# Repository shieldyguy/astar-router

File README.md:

# astar: a fast grid A* board router

A library and one binary over it, Rust, no dependencies. A scene goes in, a plan comes out.

    ./install.sh                  (cargo build --release, then ~/.local/bin/astar; CLAUDE.md has the rest)
    target/release/astar route IN.kicad_pcb -o OUT.kicad_pcb     a board in, the routed board out
    target/release/astar route SCENE.json PLAN.json [-v] [--strict]
    target/release/astar scene IN.kicad_pcb [-o SCENE.json]      the board as a scene
    target/release/astar lay BOARD.kicad_pcb PLAN.json -o OUT.kicad_pcb      a plan laid on its board
    target/release/astar --passes          the passes of a run, in order; --skip NAME leaves one out

It exits 0 when every net is joined, 1 when nets are open, 2 when the input could not be taken (and says
why), 3 when a width was narrowed and `--strict` was given. Every run checks the plan it wrote with
`astar check` before it reports: copper that breaks a rule, or a net called joined that is not, is
printed and the run exits 4 (a fault in astar, never in the board). It exits 5 when every net is joined
but KiCad will find fault that astar could not help: a custom rule it did not read that may ask more than
it kept, or a short the board came with (a pad lying on another net's copper); the lines say which. `astar SCENE.json PLAN.json` is the
old way to say the same and exits 0 whenever it wrote a plan the check finds no fault with. `docs/scene.md` is the scene, `docs/hooks.md` is how a
track adds a pass, a job kind, a cost term, a copper kind or a report entry.

astar reads a KiCad board itself (`src/io/`: KiCad 7 to the house 10.99, nets by number or by name) and
writes the plan back onto it: new copper in the file's own dialect, everything else byte for byte, the
`.kicad_pro`, `.kicad_dru` and `.kicad_prl` copied beside it unchanged. `docs/parity.md` says where its scene
differs from the house KiCad's export and why (`python3 parity/parity.py`); `python3 parity/formats.py` reads,
routes, writes and reopens a board of each file format.

`SCENE.json` and `PLAN.json` are router-bench's contract (its `CONTRACT.md`): pads, holes, outline, rules and
nets in; tracks, vias and poured planes per net out. `bench/astar.py` is the bench adapter (copy it to
`router-bench/routers/`).

## Where it stands

router-bench's five boards, judged by KiCad's DRC (`./gate.sh`, 2026-11-22). astar ran on a 2-core cloud
machine; the other two columns are the bench scoreboard's, recorded on the Mac. This repo carries dock and
g474 of the five; the other three are routed where a router-bench checkout is beside it. What astar does not
do yet is in CLAUDE.md; `corpus/SCOREBOARD.md` is the wider corpus at the same commit: 58 of 80 boards whole
with no new DRC error (the house's and the fork's own: 38 of 41; the rest are KRT's fixtures, KiCad's demos
and open boards, most of them BGA boards astar does not fan out).

| board | nets | astar | landed | new DRC | track mm | vias | krt_better | topo |
|-------|-----:|------:|-------:|--------:|---------:|-----:|-----------:|-----:|
| dock  |   28 | 2.0 s |  28/28 | 0 |  446 |  55 |  69.5 s, 443 mm |  0.1 s, 509 mm |
| g474  |   41 | 0.1 s |  41/41 | 0 |  739 | 113 |  19.4 s, 738 mm |  0.5 s, 927 mm |
| ccb   |   47 | 0.5 s |  47/47 | 0 | 1097 | 119 |  33.5 s, 1074 mm |  0.6 s, 1442 mm |
| tb150 |  118 | 1.1 s | 118/118 | 0 | 2755 | 238 |  46.5 s, 2542 mm |  1.6 s, 3524 mm |
| ub400 |  243 | 11.2 s | 243/243 | 0 | 9866 | 803 | 267.4 s, 9954 mm | 13.6 s, 12298 mm |

astar's seconds are its own (`astar route`), the judging apart. The same scene gives the same copper
every run.

## How it works

1. **Clearance field.** The board becomes a grid (0.1 mm by default). Each node of each layer holds its
   distance to the nearest copper and to the nearest copper of another net, so "may this net put a track of
   this width here" is two compares. Fixed copper (pads, holes, edge, keep-outs) and routed copper are kept
   apart, so lifting a route rebuilds only the blocks it touched.
   The grid is laid where the pads are (`route::grid_offset`): each way it is shifted, by less than a
   pitch, to where the pads' middle lines lie nearest its lines, a narrow pin counting for much more than
   a broad pad. A chip's pins then have their own grid line to run out on, and a via beside one stands
   in line with it.
2. **Fences** (topo's escapes). A pad too narrow for the grid gets an exact stub along its own centre line,
   checked against the true shapes, at its net's own width where that stands clear and else at the
   narrowest the net may be drawn. The lane in front of a fine-pitch row costs other nets a toll, and no
   foreign via may sit in its mouth.
3. **Exits** (`src/passes/exits.rs`). A long pad is left, and reached, along its length and down its
   middle: toward the inside of its part or away from it. A track that crosses such a pad's side pays
   2 mm of track for it, so it does that only where the ends are shut or far out of its way. Square pads,
   tabs that lie across their part and the two pads of a wide capacitor have no front to prefer. Style
   does not cost a net: a board that stays open with the style rules on (this one, and the price of
   crossing a pour in 10) is routed once more without them, and that board is kept when fewer of its
   nets are open (the plan's note says so). Only where that can help: when a net is open for want of
   room among the others, and the run has time left. A board whose open pads are all shut in by the
   board itself (8, below) is routed once.
4. **Plane drops.** Every surface pad of a plane net gets a short track and a via of its own beside it.
   Ending on a via or a pad the net already has costs as much as a new via (`--share`, 1.5 mm of track),
   so a pad shares one only where that is nearer than the room for its own. An exposed pad (a big pad
   inside its part's ring of pins) takes its via inside itself, on a plane net and on any other.
5. **Rail pour** (krt-better's rail_pours). The busiest rail is poured on the free inner layer (the next
   one after the ground's, where the router planned that: 10). The board is
   routed both ways at once, with the pour and without. The poured one is kept when it is whole and took
   at most a quarter more search than the plain one (and four million nodes); past that it is given up.
   The choice depends on the two boards' search work alone, never on which was done first.
6. **Search.** Weighted A* over (layer, node): eight compass steps and a via, a price for turns, a bucket
   queue. One search per pad, from the pad to the net's tree.
   A net lays its class's via (its own, where the net says one; the board's, where neither does;
   never under the board's least via and hole). Where that does not fit, the smallest via the
   board's own rules allow is laid instead (never under 0.3 mm on a 0.15 mm hole), at a price; the
   plan gives every via its size.
   A net keeps its width. Where the full width does not fit, the net may be drawn narrower, down to
   the fab's narrowest track, but a neck costs 4 mm of track to begin and four times the step along it,
   so the net goes round whatever is in its way unless the way round is longer than that. A neck is as
   wide as there is room for: while the nets are finding their ways it is drawn at its narrowest (what
   it does not take, another net may need), and once they have (9), each narrowed stretch is widened
   to the most that is clear of what stands beside it, measured exactly, to a hundredth of a
   millimetre. So a 1.5 mm rail that must pass a 0.8 mm gap is 0.5 mm there, not the fab's 0.127.
   Every neck is in the plan's notes.
7. **Negotiation.** The first pass may cross other nets at a price. Each round re-routes the nets that
   clash, with the price of a crossing and the wear of each contested node going up, until nothing clashes
   or the same nets have come up to route again for the seventh time (the same set every round, or two
   sets turn about: nets going round in a circle). A last strict pass takes off anything that still
   clashes.
   **One tolerance** (`geom::SLACK`). KiCad's DRC lets a clearance be short by 0.5 um. astar lets its
   own be short by 0.4 um of that, the same in the grid's thresholds and in every exact check of a
   piece of track against what stands beside it, pads and routed copper alike (measured exactly, piece
   against shape). So a track as wide as its pad leaves a row of pads whose gap is the board's
   clearance exactly, which a fine-pitch part on a board at its fab's limits needs.
   **A step the grid is not sure of is measured** (`Router::t_low`, `route::exact::Tight`). The grid
   says how far the nearest copper is from a node, to a hundredth, and keeps an allowance for a step
   between two nodes that sags toward a corner. Beside a straight edge there is no sag: two tracks side
   by side at exactly the clearance are legal, and the grid alone would refuse them (it sent every other
   net of a 0.4 mm row round the back). So where a node is within that allowance of the limit, the
   search measures the step itself, piece against shape, against fixed and routed copper alike; clash
   noting and pull-tight ask the same question. Seven nets at 0.2 track and 0.2 clearance run side by
   side on a 0.4 pitch (`tests/scenes/lanes.json`).
   **True ends** (`src/route/ends.rs`). A path is drawn as it is laid, and its ends are drawn where the
   copper they join is, not at the grid node beside it: the end leg runs on the line through the pad's
   centre (out of a pin: on the pin's middle line), and the corner at its other end slides along the
   next leg to meet it, so both legs keep their headings. A leg that runs straight into a via or a track
   of its net ends in that copper, on its own line. Each piece moved off the grid is checked against the
   exact shapes; where it is not clear the end is laid as the grid found it, and the plan's notes count
   those.
   **Copper already there** (`src/route/old.rs`). The tracks and vias a board comes with stay where
   they are and are part of their nets. What they join is joined: pads and pieces that touch (as KiCad
   counts it: their copper overlaps on a layer both are on, so a track whose round end lies on a pad,
   a track that runs over one, two tracks that cross, and two pads that lie on each other with no track
   at all) are one island, and an island comes into its net's tree whole. Pads it joins get no track;
   the gate asks KiCad the same question of the same copper (`tests/touch_judge.py`). A new track may start anywhere on it and end anywhere
   on it, drawn to the old copper's own line. A piece no pad stands on is joined to its net like a pad
   (KiCad counts it open otherwise); one that cannot be is in the plan's notes (`loose`). On a plane
   net, a pad that old copper takes to a via in the plane needs no via, and pads joined by a track
   share one. So wiring laid first (the short runs of `pcb wire --near --easy`, a fanout, a stamped
   block) is kept and built on.
8. **Mending** (`src/route/mend.rs`). A net the rounds left open is laid through whatever stands in its
   way, what it went through is lifted and routed again round it, two deep. The move is kept only when
   fewer pads are open after it; else the board is put back exactly as it was, and the next try keeps
   off the nets the last one went through: the room a net needs is sometimes held by a net nobody has
   clashed with (a rail that ran along the front of a row of pads).
   A net left open says why (`src/route/solve.rs`). When the searches for a pad find no way, a flood
   from the pad over every node a track of the net may stand on as far as what stays goes (pads, edges,
   keep-outs, fences, copper the board came with) asks the board whether it leaves one at all. Where
   it leaves none, the pad is shut in by the board itself: it is not tried again, in the rounds or
   here, and the run says `the board itself leaves no way to U1.2`, which is a matter for the placement
   or the rules, and names what stopped the flood, nearest the pad first (`src/route/wall.rs`): `U1.2
   is shut in by pad U1.3 (SCK) and a keep-out`. Else it says no way was found among the other nets,
   and whose copper is in the way: last of all, each net still open is laid once more, free to run
   through other nets' copper, the nets it runs through are noted with the place, and the board is
   put back as it was (`Router::blame`): `the nearest way runs through NRST at (24.10, 18.30)`.
9. **Redrawing** (`src/route/redraw.rs`). How a path is drawn depends on what stood beside it when it
   was laid: a stretch narrowed, an end laid as found, a whole path kept as the search found it because
   it ran through another net's copper (wiggles and all). That is often copper since lifted. So once
   the rounds are over, before the mending and again after it, every net drawn with such a concession
   is pulled tight and drawn again from its paths, against the board as it stands; the joints of its
   tree stay where they are. After the mending that is done for every net: a track that stepped aside
   for a neighbour which was then routed another way is drawn straight again. The new drawing is kept only when it is clear
   of what has been laid since; else the net keeps the drawing it had.
10. **Pours** (`src/route/fill.rs`). A net the board pours copper for leans on that copper: astar works out
   where KiCad will fill the pour round the copper that stands, which pads the fill joins (solid, or
   through the spokes of a thermal relief as KiCad builds them), and lays track only for what is left; a
   track may end anywhere in the fill. Where other nets later cut the fill, the net is routed again. A
   relief left with too few spokes gets a short track of its own from the pad into the fill, which is
   what KiCad's DRC asks for.
   A pour is copper to go down into, as a plane is: the net's tree starts in the pour's largest piece,
   so each pad reaches the pour the shortest way it can (a stub and a via when the pour is on the other
   side) and no pad is first wired to another across it.
   **Crossing** (`src/passes/cross.rs`). A pour is copper someone meant to be there: a ground under the
   signals, a wide path for a current. A step across another net's pour costs twice a step beside it
   (`--cross`), so a track cuts a pour where the way round is dearer and no further than it must. Where
   every layer is poured nothing is charged: there no layer is the better one to cross on.
   **The board is the declaration, and what it leaves unsaid the router plans** (`src/passes/ground.rs`).
   What a net's copper should be is read off the board first: a zone drawn for a net is its pour, a layer
   given to a net is its plane. What the board leaves undrawn of its ground is drawn the house way:
   the first free inner layer as its plane (where the board gives it no inner layer) and, over a
   plane, a pour on each outer layer (where the board pours the ground on neither); on a board with
   no inner layer, one pour on the side with fewer parts. Each is drawn over the whole board and
   relieved at its pads by 10 mil spokes over a 10 mil gap. The board is then routed as if that had
   been drawn: under a plane every ground pad goes a via down, and the outer pours fill what the
   tracks leave (they are not priced to cross: the plane is what lies under the signals, and a pad
   they leave fewer than two spokes gets a short track into them, 9). The plan says so (`planned`),
   and each plane or pour is written to the board as a zone. A plane meets its net's through-hole pins by the same reliefs (a plane the
   board draws, by its own zone's): where other nets' pins or vias leave such a pin fewer than two
   spokes, it gets short tracks of its own on the plane's layer, as a pad in a pour does (9). `--plane 'GND=In1.Cu,+3V3=In2.Cu'` gives any net its layers outright (an inner layer is a
   plane, an outer one gets a pour; `--plane 'GND=In1.Cu+B.Cu'` is both). `--ground tracks` wires the
   ground as any net is, and the notes say so (`ground`).
   On the 29 house and fixture boards whose ground has nothing drawn, the planned pour cut the track by
   a fifth (5,859 mm to 4,589 mm) with the same nets joined, and KiCad's verdict after a refill was the
   same on every one: no error and no open net that the wired board did not have. The outer pours over
   a plane change no track and no via, and KiCad's verdict on the 41 boards stays as it was.
   **Pairs** (`src/route/duo.rs`). A differential pair is two nets that run side by side between the two
   parts both have a pad on (the connector or its ESD array, the chip). Between them the pair is one
   thing in the negotiation: a centre line, searched as a net of its own that keeps half the pair's
   breadth more from everything than a plain net does, and the two tracks drawn off it, one to each
   side, at the pair's width and gap (the pair's own, else its class's; the gap never under the
   clearance). The line pays for what it runs through like any path, so the pair and its neighbours
   settle who gives way by price; lifting either net lifts both. Each net's pads are then joined to
   the nearer end of its track like any net's. A pair stays on its pads' layer. One that cannot be
   laid so (its pads lie the other way round at one end, the only way is the long way round, its
   pads are on both sides) is routed as two plain nets, and the plan says which and why (`pair`,
   `astar: pair: ...` on stderr); a laid pair's note gives its length side by side and how much
   longer one half is. The two halves are not made the same length. `--skip pairs` routes every
   pair as two nets. A pair the board already carries track of is not laid again. A pair is style, as a pad left by its end is: a board that stays open with its
   pairs side by side is routed once more with every pair as two nets, and that board is kept when
   fewer of its nets are open. Of the 13 pairs on the house, fixture and bench boards 7 are laid side by
   side, with the same nets joined and the same verdict from KiCad as before.
   **Some nets only** (`--nets`, `--except`, the scene's `scope`). The nets asked for are routed; the
   others get no copper and are not counted as open. They are still on the board: their pads and their
   copper are fixed copper to the nets that are routed, and their fine-pitch pins keep their fences and
   lanes, so the way out of them is still there for whoever routes them next. The plan names them
   (`not_asked`).
   **The layers a net is routed on** (`--route-on 'CLK*=B.Cu'`, a net's `route_on` in the scene). Its
   tracks run on the layers named and nowhere else, in every search and in the redrawing. Its vias are
   not part of it: a through via goes through every layer, as always. A pad of the net on another
   layer is left by a stub to a via: off its layers the net may stand only within `--stub` (2.5 mm)
   of the copper of a pad of its own on that layer, and a step there costs three, so the stub is as
   short as there is room for. A rule that cannot be kept leaves the net open, and the run says the
   rule is what shuts the pad in. The plan records the rule (`route_on`) and its notes say how much of
   the net runs where; astar's own check holds the plan's copper to it (`layer`).
   Where 2.5 mm comes from: every signal net of the 38 boards in `corpus/boards`, 426 of them, was
   kept to the bottom layer by itself. All 426 were joined at 2.5 mm, and at 4 and 6 mm too; with room
   to spare the longest stub ran to 5.9 mm, and the shorter limit gave less track off the layer in all.
   **Drops** (`--drops NET`). A block laid out alone has no pour of its own: its ground is the pour of
   the board it will be set into. Such a net's pads go down by vias (a pad may share one, and old copper that reaches a via counts) and nothing else, the vias
   are joined by nothing here (the notes say so, `drops`), no zone is drawn for it, and the layer the
   vias go down to stays open to tracks, at the crossing price.
11. **Pull tight.** Each path is redrawn as the fewest straight runs and 45° elbows the field allows, never
   with more of it too tight for the full width than it had, never through more of another pin's lane
   than it had (the search paid to keep out of it), and never across the side of a pad that the search
   left by an end. At a pad the track runs straight on and the bend goes to the far end of the
   stretch: out of a pin, straight for as far as it can go. This pass decides the look.
12. **Round** (krt-better's round_corners). Every corner becomes an arc of one radius (`--radius`, 1 mm; 0
   keeps them sharp), checked with exact geometry against all other copper. The biggest radius is tried on
   every corner first, so tracks that turn together keep their spacing through the bend. About nine
   corners in ten round; the rest are at pads, vias and branches, or have no room.

## What it does not do yet

The plan to close these, and the rest of the distance to KRT, is in `plan/` (start at `plan/README.md`).

- The ground and one rail get a plane or a pour; the other rails are track.
- Vias are not shared by plan: every pad of a plane net gets a via of its own, though the ground's outer
  pours would let far fewer do (`--share` only prices a drop that ends on a via already there). A way
  to say which pads share one is not there.
- A two-layer board gets its ground poured on one side, not both. On both, a chip's ground pin beside
  its exposed pad is left one spoke (its spoke and the pad's meet head on, which astar's picture of
  the fill does not show), and KiCad faults it (`starved_thermal`).
- Other nets' tracks are not kept off a relief's spokes by any price; a relief left one spoke gets a
  track of its own only where a straight one from the pad reaches fill.
- Copper already on the board is never lifted: a net whose old copper is in another's way is not
  routed again. The fill a zone was last given is not read; astar works the fill out itself (10).
- A differential pair runs side by side on one layer only, and its halves are not length-matched; a
  match group and an impedance target are carried and not used.
- A clearance asked on one layer only, or between two classes only, is kept everywhere (the largest of
  them): legal, and more room than the rule asks. A track width for one layer is not used.
- A net is as wide as its class says. A net that is power by its name and no wider than a signal is
  named (`astar: thin: ...`); nothing widens it but a net class.
- The tuning is for the 0.1 mm grid, the only one judged by DRC. By its own count: at 0.05 mm dock lands
  27 of 28 and ub400 takes 14 s; at 0.2 mm ub400 takes 1.3 s but dock and ccb leave fine-pitch pins open.
- The same five boards on two layers with no planes (ground as track), by its own count: four land
  whole in under a second, ub400 lands 242 of 243 in 21 s.

## Files

    src/main.rs      the command line                    src/route/     the router: the run (drive), jobs,
    src/lib.rs       the library: astar::route(scene,                   negotiation, laying and lifting
                     &cfg), Scene, Cfg, Routed, Error                   copper, old copper, the exact index
    src/scene/       the scene: types, the readers of    src/passes/    the pass hook and one file a planning
                     1.1 and 2, the validator                           pass: pour, fences, exits, cross, drops
    src/geom.rs      shapes and distances                src/finish/    pull tight; corners into arcs
    src/field/       the clearance field, copper kinds   src/report/    notes, counts, open nets, the plan
    src/search/      the A*, its queue, the cost hook    examples/      a scene routed through the library
    src/json.rs      a small JSON reader and writer      docs/          scene.md (scene 2), hooks.md (the five
    bench/           the bench adapter; a board writer                  hooks, errors and exit codes)
                     for machines without braid-field    tests/         same.sh and golden/ (the bench five's
                     (BENCH_FIELD_PY=bench/shim)                        copper), scene.rs, lib.rs, cli.rs,
                                                                        fuzz.rs, scenes/ (the fixtures)

## Licence

Apache-2.0 (`LICENSE`, `NOTICE`).

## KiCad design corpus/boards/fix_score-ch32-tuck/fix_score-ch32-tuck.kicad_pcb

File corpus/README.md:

# corpus: the boards astar is proved on

Whose the boards are decides where they may go (Chris's list, 2026-11-18):

- **May be public**: dock, g474, every `house_*`, every `fix_*`, every `qa_*`.
- **Private**: ccb, tb150, ub400 and every `demo_*`. They stay out of a public repository, in every commit.
- **Not ours to pass on**: every `krt_*` (KRT's own boards) and the stress boards (third parties'). They are
  left out of any repository but the fork of KRT's.

This repository carries the first group only. The other boards keep their rows in the manifest and the
baseline (`committed` false); `prepare.py NAME` makes them in `boards/` from a router-bench, kicad or KRT
checkout on the machine, where `boards/.gitignore` keeps them out of a commit.

What is here:

    manifest.json     every board with its facts (source, layers, nets, zones, class) and where it came from
    boards/NAME/      the bare board, its project, its scene, the bare board's own DRC (made by prepare.py)
    prepare.py        makes boards/ and the manifest from the boards on this machine
    fetch_stress.py   fetches KRT's stress corpus (open boards on GitHub) into a cache outside the repo
    run.py            astar over the corpus, each board judged by KiCad; rows.jsonl
    baseline.jsonl    the last whole run's rows: what "no worse" is measured against
    scoreboard.py     the baseline as a page (SCOREBOARD.md): a row a board, a summary by source and by failure class
    smoke.txt         the boards the gate's smoke run routes and judges (`./gate.sh --smoke`)

Third-party boards (source `stress`: KRT's stress sets, fetched from their public repositories) are **not
committed**: the manifest names each one's repository, commit and path, `fetch_stress.py` gets it again, and
the files live in a cache outside the repo (`/home/claude/corpus-cache`, or `$ASTAR_CORPUS_CACHE`). Their
licences are their owners'; nothing is pushed to those repositories.

Not committed either: `out/` (plans, routed boards and DRC reports of the last run), `rows.jsonl`, and the
boards larger than 1.5 MB (`boards/.gitignore`; `prepare.py NAME` makes them again).

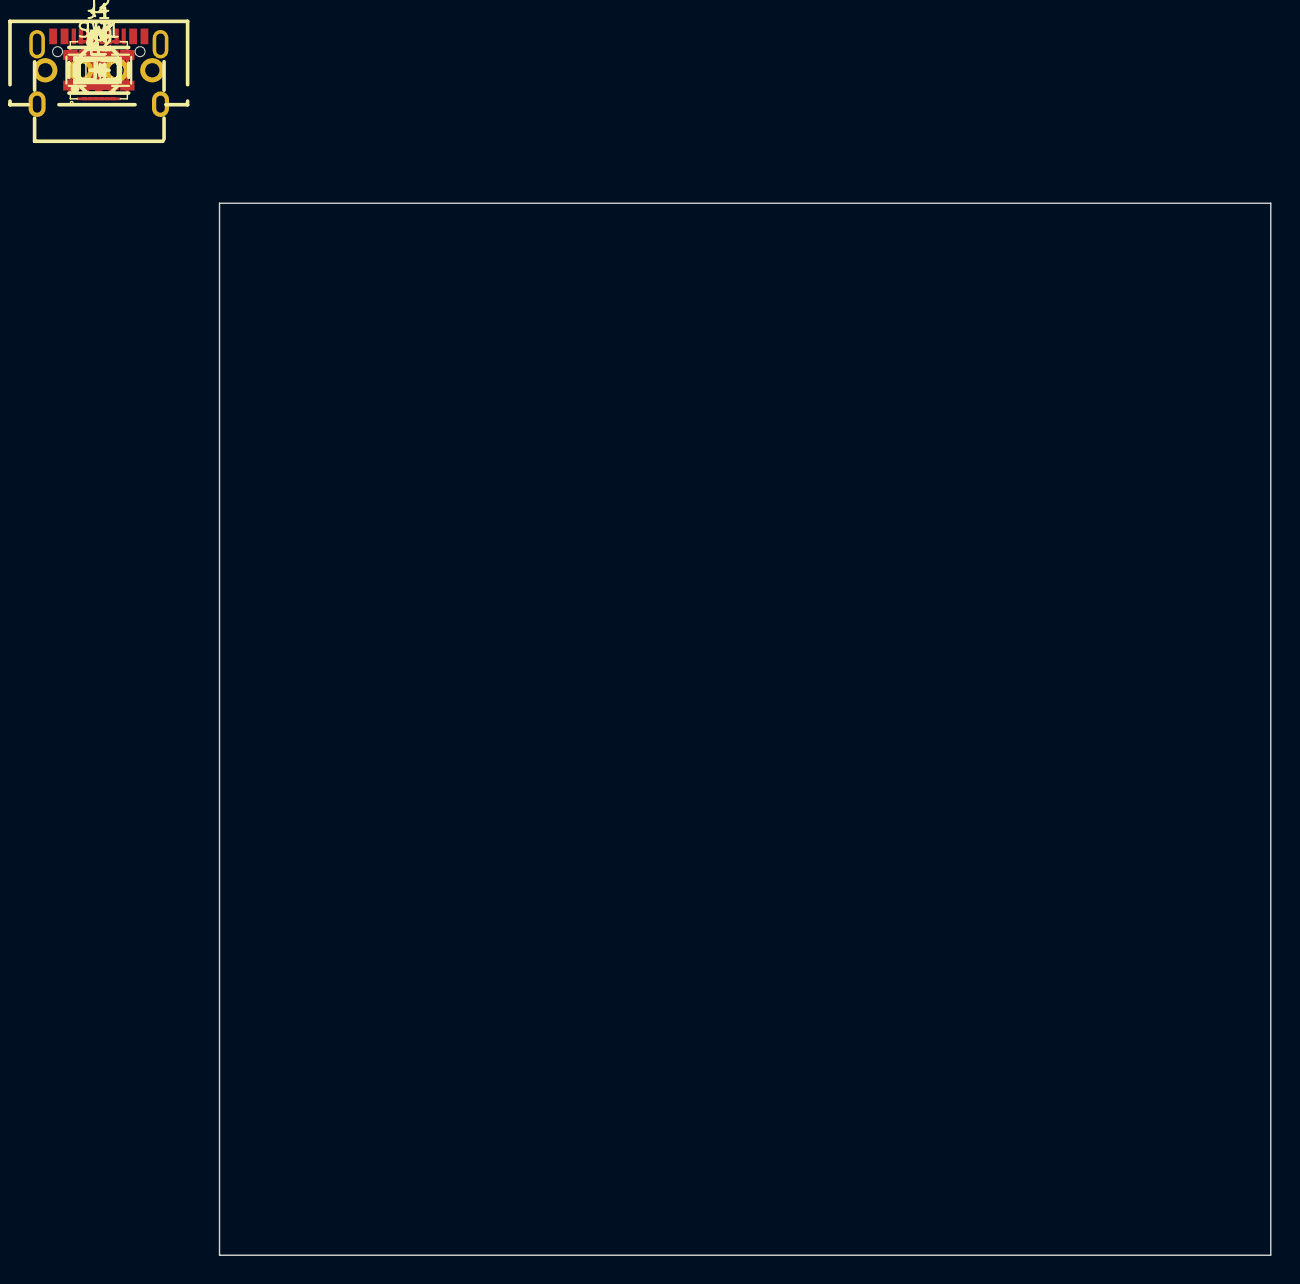
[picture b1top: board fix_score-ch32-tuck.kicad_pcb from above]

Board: 2 copper layers, 73.7 x 73.7 mm, 15 parts (0 on the bottom side), 16 nets, no tracks yet.

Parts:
C1: 10uF; C0603
C2: 1uF; C0603
D1: B5819W SL; SOD-123_L2.7-W1.6-LS3.7-RD-1
D2: RUN; LED-SMD_L1.6-W0.8-R-RD
F1: JK-nSMD050-30; F1206
J1: USB-C; USB-C-SMD_TYPE-C-16PIN-2MD-073
J2: DEBUG; CONN-TH_B4B-XH-A-LF-SN
R1, R2, R3: 5.1kΩ; R0603
R4: 1kΩ; R0603
SW1: BOOT; SW-SMD_4P-L4.2-W3.2-P2.15-LS4.5
U1: CH32X035G8U6; QFN-28_L4.0-W4.0-P0.40-BL-EP2.8
U2: USBLC6-2SC6; SOT-23-6_L2.9-W1.6-P0.95-LS2.8-BL
U3: LP5907MFX-3.3/NOPB; SOT-23-5_L3.0-W1.7-P0.95-LS2.8-BR

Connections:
+3V3: C1.1, J2.1, SW1.3, U1.2 (VDD), U3.5 (OUT)
+5V: C2.1, D1.1, U3.1 (IN), U3.3 (EN)
BOOT_EN: R1.2, SW1.1
CC1: J1.A5 (CC1), R2.1
CC2: J1.B5 (CC2), R3.1
GND: C1.2, C2.2, D2.2, J1.13 (EH), J1.14 (EH), J1.A1B12 (GND), J1.B1A12 (GND), J2.4, R2.2, R3.2, U1.29 (GND), U2.2, U3.2 (GND)
LED: R4.1, U1.23 (PB12/T1C4_/T2C2N_)
LED_A: D2.1, R4.2
SWCLK: J2.3, U1.24 (PC19/DCK/T2C1_/T3C1_/I2C_/RX3_/C1P0)
SWDIO: J2.2, U1.25 (PC18/DIO/TX3_/T2C1N_/T3C2_/I2C_/T1ET_)
USB_DM: U1.26 (PC16/UDM/T1C4/TX4_/I2C_/RX4_/CTS1/PC11), U2.6
USB_DM_C: J1.A7 (Dn1), J1.B7 (Dn2), U2.1
USB_DP: R1.1, U1.27 (PC17/UDP/RTS1/TX4_/I2C_/RX4_/T1ET/PC10), U2.4
USB_DP_C: J1.A6 (Dp1), J1.B6 (Dp2), U2.3
VBUS_C: F1.1, J1.A4B9 (VBUS), J1.B4A9 (VBUS), U2.5
VBUS_F: D1.2, F1.2

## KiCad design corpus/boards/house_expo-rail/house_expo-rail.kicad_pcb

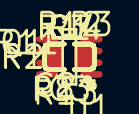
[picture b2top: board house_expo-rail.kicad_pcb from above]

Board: 2 copper layers, 14 parts (0 on the bottom side), 9 nets, no tracks yet.

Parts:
C1: 100nF; CC0603KRX7R9BB104
C2: 47nF; CL10B473KB8NNNC
C3: 1nF; CL10B102KB8NNNC
Q1: PAIR; DMMT3906W-7-F
R1: 4.7MΩ; 0603WAF4704T5E
R2: 62kΩ; 0603WAF6202T5E
R3: 39kΩ; 0603WAF3902T5E
R7, R11: 100kΩ; 0603WAF1003T5E
R8: 91kΩ; 0603WAF9102T5E
R12: 18kΩ; 0603WAF1802T5E
R13: 470Ω; 0603WAF4700T5E
R14: 75kΩ; 0603WAF7502T5E
U1: TLV9152; TLV9152IDDFR

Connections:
GND: C1.2, C3.2, R1.1, R3.2, U1.4
unnamed: C2.1, Q1.2, R2.1, R13.1, U1.7
unnamed: C2.2, R11.2, U1.6
unnamed: C3.1, Q1.3, R1.2, U1.5
unnamed: Q1.1, R12.1, R13.2
unnamed: R2.2, R3.1, U1.3
unnamed: R12.2, R14.2, U1.1
unnamed: R7.2, R8.2, R14.1, U1.2
VCC: C1.1, Q1.4, Q1.5, U1.8

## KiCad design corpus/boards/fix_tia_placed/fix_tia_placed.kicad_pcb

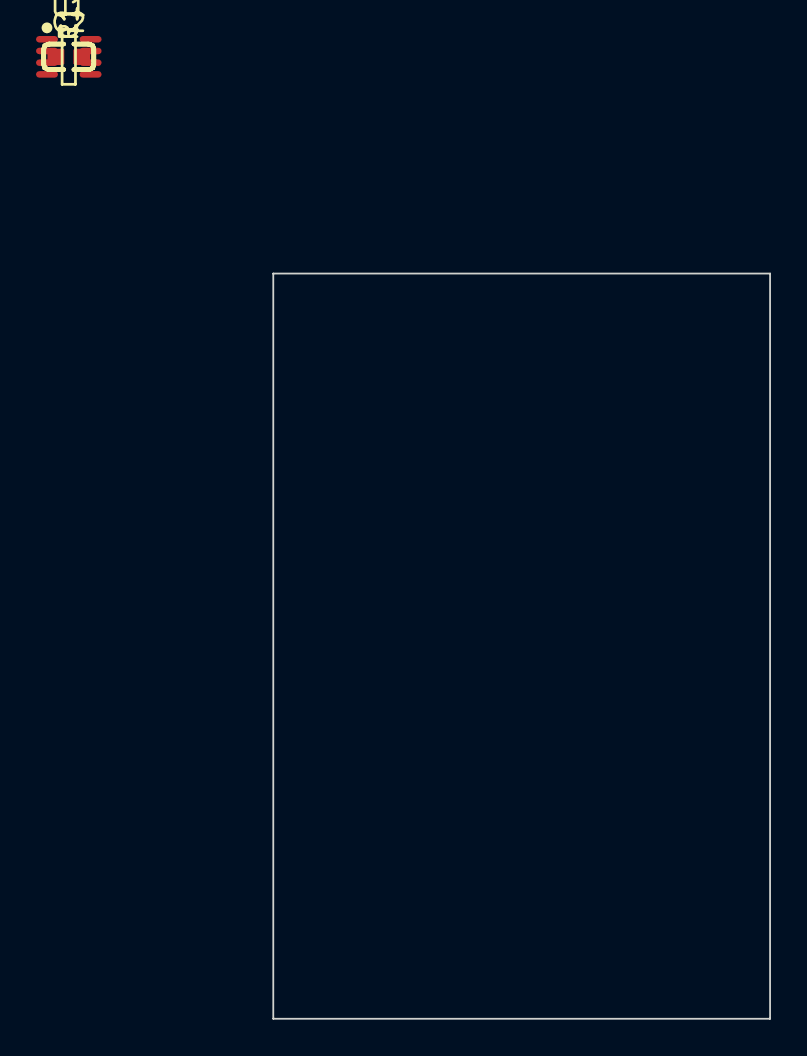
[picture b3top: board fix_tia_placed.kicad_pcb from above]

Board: 2 copper layers, 27.6 x 41.4 mm, 4 parts (0 on the bottom side), 4 nets, no tracks yet.

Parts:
C1: 10pF; C0603
C2: 100nF; C0603
R1: 1MΩ; R0603
U1: TLV9002; TSOT-23-8_L2.9-W1.6-P0.65-LS2.8-TL

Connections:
GND: C2.2, U1.4
ISIG: C1.1, R1.1, U1.2
OUT: C1.2, R1.2, U1.1
VCC: C2.1, U1.8

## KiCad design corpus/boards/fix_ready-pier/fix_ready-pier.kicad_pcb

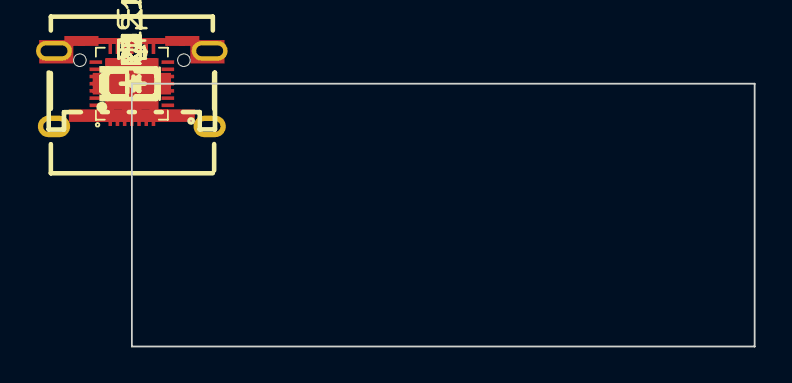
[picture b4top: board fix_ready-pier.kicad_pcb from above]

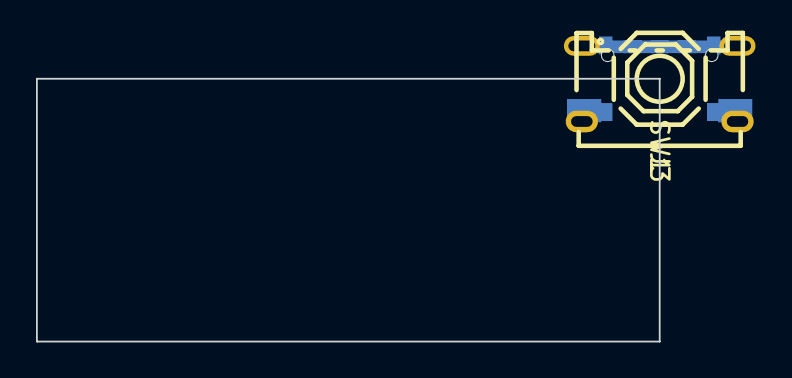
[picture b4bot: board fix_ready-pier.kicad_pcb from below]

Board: 2 copper layers, 34.6 x 14.6 mm, 14 parts (2 on the bottom side), 16 nets, no tracks yet.

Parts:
C1: 100nF; C0603
C3: 10uF; C0603
D1: B5819W SL; SOD-123_L2.7-W1.6-LS3.7-RD-1
D4: LED; LED-SMD_L1.6-W0.8-R-RD
J1: USB-C; USB-C-SMD_TYPE-C-16PIN-2MD-073
J2: CHAIN_A; CONN-SMD_4P-P1.50_S4B-ZR-SM4A-TF-LF-SN
J3: CHAIN_B; CONN-SMD_4P-P1.50_S4B-ZR-SM4A-TF-LF-SN
R1, R2: 5.1kΩ; R0603
R3: 5.1k; R0603
R5: 1kΩ; R0603
SW1: BOOT; SW-SMD_4P-L5.1-W5.1-P3.70-LS6.5-TL_H1.5
U1: CH32X035G8U6; QFN-28_L4.0-W4.0-P0.40-BL-EP2.8
U2: USBLC6-2SC6; SOT-23-6_L2.9-W1.6-P0.95-LS2.8-BL

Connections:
+5V: C1.1, C3.1, D1.1, J2.1, J3.1, SW1.3, U1.2 (VDD)
/LED: R5.1, U1.28 (PC14/CC1/T1C3_/T2C2_)
/U1RX: J2.3, U1.22 (PB11/T1C3/T2C1N_/RX1)
/U1TX: J2.2, U1.21 (PB10/TX1/T1C2)
/U2RX: J3.3, U1.8 (PA3/T2C4/O1O0/T3C1_/RX2/A3)
/U2TX: J3.2, U1.7 (PA2/TX2/T2C3/O2O1/T2ET_/A2)
/USB_DM: U1.26 (PC16/UDM/T1C4/TX4_/I2C_/RX4_/CTS1/PC11), U2.6
/USB_DP: R3.1, U1.27 (PC17/UDP/RTS1/TX4_/I2C_/RX4_/T1ET/PC10), U2.4
BOOT_EN: R3.2, SW1.1
CC1: J1.A5 (CC1), R1.1
CC2: J1.B5 (CC2), R2.1
GND: C1.2, C3.2, D4.2, J1.13 (EH), J1.14 (EH), J1.A1B12 (GND), J1.B1A12 (GND), J2.4, J2.5, J2.6, J3.4, J3.5, J3.6, R1.2, R2.2, U1.29 (GND), U2.2
LED_A: D4.1, R5.2
USB_DM_C: J1.A7 (Dn1), J1.B7 (Dn2), U2.1
USB_DP_C: J1.A6 (Dp1), J1.B6 (Dp2), U2.3
VBUS: D1.2, J1.A4B9 (VBUS), J1.B4A9 (VBUS), U2.5

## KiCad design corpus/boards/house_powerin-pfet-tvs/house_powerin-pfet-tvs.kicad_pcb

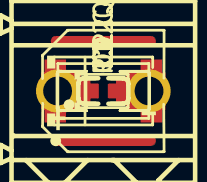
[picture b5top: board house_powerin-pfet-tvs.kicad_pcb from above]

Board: 2 copper layers, 9 parts (0 on the bottom side), 4 nets, no tracks yet.

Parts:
C1, C2: 10uF; CL31B106KBHNNNE
C3: 100nF; CC0603KRX7R9BB104
C4: 100uF; RVT1H101M0607
D1: 15V; BZT52C15
D2: 26V; SMBJ26A
J1: PWR-IN; DB128L-5.08-2P-GN-S
Q1: P-FET; AO4407A
R1: 100kΩ; 0603WAF1003T5E

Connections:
GND: C1.2, C2.2, C3.2, C4.2, D2.2, J1.2, R1.2
unnamed: J1.1, Q1.5, Q1.6, Q1.7, Q1.8
unnamed: D1.2, Q1.4, R1.1
VIN: C1.1, C2.1, C3.1, C4.1, D1.1, D2.1, Q1.1, Q1.2, Q1.3

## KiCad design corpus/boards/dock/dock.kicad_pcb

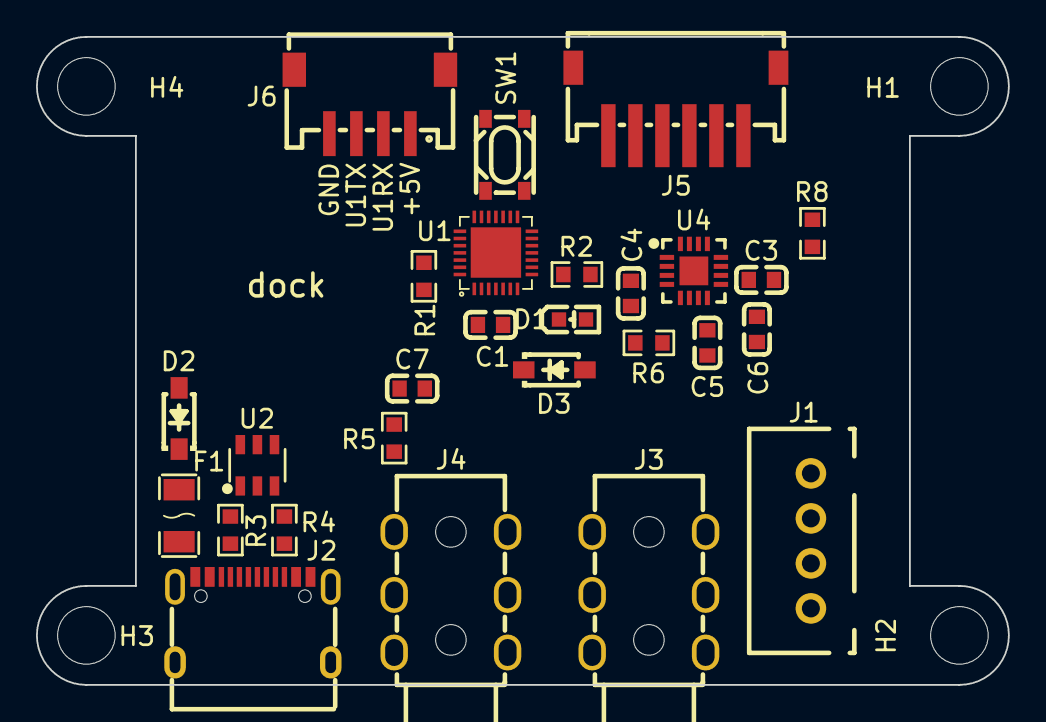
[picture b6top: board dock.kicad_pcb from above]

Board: 4 copper layers, 54.0 x 36.0 mm, 31 parts (0 on the bottom side), 28 nets, no tracks yet.

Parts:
C1: 10uF; CL10A106MA8NRNC
C3, C4: 2.2uF; CL10A225KA8NNNC
C5, C6: 1uF; CL10A105KB8NNNC
C7: 100nF; CC0603KRX7R9BB104
D1: RUN; KT-0603R
D2, D3: B5819W SL; B5819W_SL
F1: JK-nSMD050-30
H1, H2, H3, H4: MountingHole_3.2mm_M3
J1: DEBUG; B4B-XH-A(LF)(SN)
J2: USB-C; TYPE-C_16PIN_2MD(073)
J3: OUT; PJ-3136-B
J4: SUSTAIN; PJ-3136-B
J5: DSP_AUDIO; S6B-ZR-SM4A-TF(LF)(SN)
J6: DSP_LINK; S4B-ZR-SM4A-TF(LF)(SN)
R1, R3, R4: 5.1kΩ; 0603WAF5101T5E
R2: 1kΩ; 0603WAF1001T5E
R5: 10kΩ; 0603WAF1002T5E
R6, R8: 100kΩ; 0603WAF1003T5E
SW1: BOOT; GT-TC048D-H025-L1
U1: CH32X035G8U6
U2: USBLC6-2SC6
U4: TPA6132A2; TPA6132A2RTER

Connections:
+5V: C1.1, C3.1, D2.1, D3.1, J1.1, J6.1, R6.2, SW1.3, U1.2 (VDD), U4.6 (G0), U4.14 (VDD)
AUX_L: J5.2, U4.1 (INL-)
AUX_R: J5.3, U4.4 (INR-)
GND: C1.2, C3.2, C4.2, C5.2, C7.2, D1.2, J1.4, J2.13 (EH), J2.14 (EH), J2.A1B12 (GND), J2.B1A12 (GND), J3.2, J4.2, J4.3, J5.0, J5.1, J5.4, J6.4, R3.2, R4.2, R8.2, U1.29 (GND), U2.2, U4.2 (INL+), U4.3 (INR+), U4.7 (G1), U4.10 (PGND), U4.15 (SGND), U4.17 (EP)
HP_EN: R8.1, U1.12 (PA7/MOSI/T3C2/T1C1N_/TX1_/O2P0/A7), U4.13 (EN)
HP_OUT_L: J3.4, U4.16 (OUTL)
HP_OUT_R: J3.3, U4.5 (OUTR)
MCU_SWCLK: J1.3, U1.24 (PC19/DCK/T2C1_/T3C1_/I2C_/RX3_/C1P0)
MCU_SWDIO: J1.2, U1.25 (PC18/DIO/TX3_/T2C1N_/T3C2_/I2C_/T1ET_)
MCU_USB_DM: U1.26 (PC16/UDM/T1C4/TX4_/I2C_/RX4_/CTS1/PC11), U2.6
MCU_USB_DM_C: J2.A7 (Dn1), J2.B7 (Dn2), U2.1
MCU_USB_DP: R1.1, U1.27 (PC17/UDP/RTS1/TX4_/I2C_/RX4_/T1ET/PC10), U2.4
MCU_USB_DP_C: J2.A6 (Dp1), J2.B6 (Dp2), U2.3
unnamed: D1.1, R2.2
unnamed: D2.2, F1.2
unnamed: J2.A5 (CC1), R3.1
unnamed: J2.B5 (CC2), R4.1
unnamed: J4.4, R5.1
unnamed: R1.2, SW1.1
unnamed: R2.1, U1.23 (PB12/T1C4_/T2C2N_)
unnamed: C6.2, U4.9 (CPN)
unnamed: C6.1, U4.11 (CPP)
unnamed: C4.1, U4.12 (HPVDD)
unnamed: C5.1, U4.8 (HPVSS)
SUS: C7.1, D3.2, R5.2, R6.1, U1.11 (PA6/MISO/T3C1/T1BK_/O1N0/A6)
U1RX: J6.2, U1.22 (PB11/T1C3/T2C1N_/RX1)
U1TX: J6.3, U1.21 (PB10/TX1/T1C2)
VBUS_C: F1.1, J2.A4B9 (VBUS), J2.B4A9 (VBUS), U2.5
